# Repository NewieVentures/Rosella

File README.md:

# Rosella (code name Project Faraday)
### By NewieVentures

Remote control of LED strip lights via DMX over cellular.

## Hardware
### Artifacts
* FP1 - Motherboard
* FP2 - DMX expansion module
* FA1 - Assembled unit
* FA2 - Demonstration panel

## LED patterns
To update the pattern of an active device, the device ID and a valid access token is required:

`curl -v "https://api.particle.io/v1/devices/<DEVICE_ID>/<function>" -d access_token=<TOKEN> -d arg=<ARG>`

eg to set a green strobe at 1Hz:

`curl -v "https://api.particle.io/v1/devices/<your device ID here>/strobe" -d access_token=<your access token here> -d arg="1000,#00FF00"`

### Blink
Flash LEDs on and off. Duty cycle controls amount of time on vs off.
#### Arguments
`"<period (ms)>,<duty cycle (0-100)>,<colour-on>,<colour-off>"`

eg blink red 1s:

`POST /v1/devices/:deviceId/blink { "arg": "1000,50,#FF0000,#000000" }`

### Colour
Fixed colour on all leds
#### Arguments
`"<colour>"`

Eg all LEDS blue:

`POST /v1/devices/:deviceId/colour { "arg": "#0000FF" }`

### Gradient
Linear colour gradient
#### Arguments
`"<start-colour>,<end-colour>"`

eg gradient on all LEDS from red to green:

`POST /v1/devices/:deviceId/gradient { "arg": "#FF0000,#00FF00" }`

### Progress
Progress bar
#### Arguments
* Initial value: 0 - (# leds – 1)
* Final value: 1 - #leds
* Direction: 0 = first LED to last, 1 = last LED to first

`"<initial value>,<final value><increment (# leds)>,<increment delay (ms)>,<reset delay(ms)>,<direction>,<colour-on>,<colour-off>"`

eg Progress bar from 0 to 100 leds with 1s between increments, 5s pause at the final value
before repeating and starting from the first LED to the last, incrementing by 1 LED with
RED being on and black being off:

```
POST /v1/devices/:deviceId/progress
{ "arg": "0,100,1,1000,5000,0,#FF0000,#000000" }
```

### Snake
Block of LEDS moving along the strip.
#### Arguments
* Direction: 0 = first LED to last, 1 = last LED to first
`"<period (ms)>,<direction>,<length (# leds)>,<colour-on>,<colour-off>"`

eg Green block of 3 LEDS moving from first LED to last every 5s on a black background:

`POST /v1/devices/:deviceId/snake { "arg": "5000,0,3,#00FF00,#000000" }`

### Strobe
Flash LEDs
#### Arguments
`"<period (ms)>,<colour>"`

eg Blue flash at 1Hz

`POST /v1/devices/:deviceId/strobe { "arg": "1000,#0000FF" }`

## Firmware
The firmware is compiled using the particle cloud development tools (internet connection required).

### Setup
Install the particle CLI, see docs at
https://docs.particle.io/tutorials/developer-tools/cli/

### Compiling
To compile using the particle CLI:
`particle compile electron app --saveTo electron.bin`

### Flashing
To flash a binary to the module over USB, put it into programming mode then:
`particle flash --usb electron.bin`

### Unit tests
```
cd src
make tests && ./tests
```

### Structure
The firmware runs on a Particle Electron board, using their Device OS.  The major firmware modules are:
* cloudFunctions - functions registered with Particle's Device OS on boot and called via their cloud interface.
* LedStripDriver - generates colour values for each LED based on the pattern and settings.  The cloud functions change the pattern settings, while a timer in the RTOS calls the onTimerFired() method to process the new values.
* dmx - uses Serial1 to send the DMX packets (requires some low level override of the baud rate to send the break and mark-after-break at the start of the packet) and sends the NULL start code in each packet.

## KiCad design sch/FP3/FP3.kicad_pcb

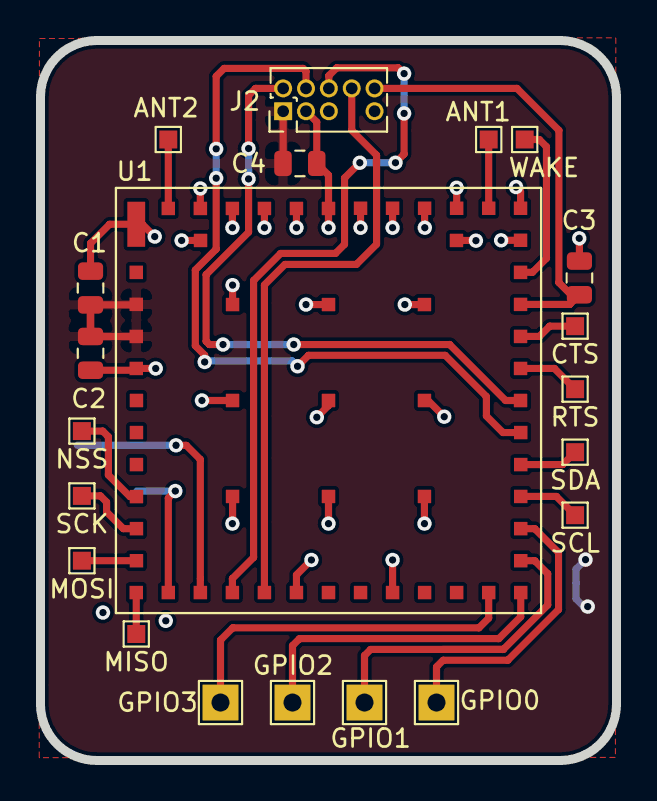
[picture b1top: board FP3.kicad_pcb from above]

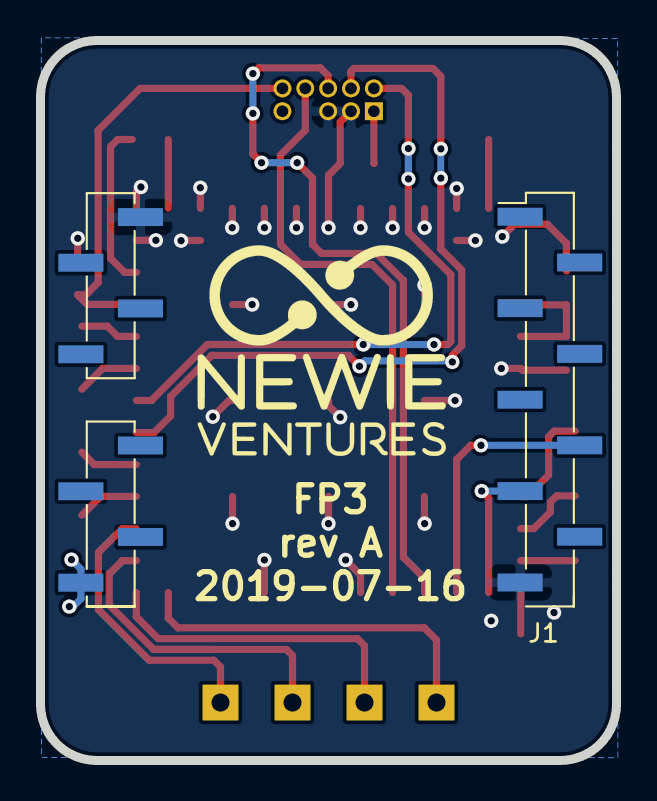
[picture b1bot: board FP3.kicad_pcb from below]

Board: 2 copper layers, 32.0 x 40.0 mm, 23 parts (2 on the bottom side), 24 nets.

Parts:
C1: 10uF 10V; R_0805_2012Metric
C2, C3, C4: 100nF 50V; R_0805_2012Metric
G1: Logo-NewieVentures-75px; logo_14.2x12.1mm
J1: module_connector_header; Faraday_module_smt_hdr
J2: MXDOT_Prog_Header_Keyed; Header_MDOT_PROG_2x05_Pitch1.27mm
TP1: GPIO3; TestPoint_THTPad_2.0x2.0mm_Drill1.0mm
TP2: GPIO2; TestPoint_THTPad_2.0x2.0mm_Drill1.0mm
TP3: GPIO1; TestPoint_THTPad_2.0x2.0mm_Drill1.0mm
TP4: GPIO0; TestPoint_THTPad_2.0x2.0mm_Drill1.0mm
TP5: WAKE; TestPoint_Pad_1.0x1.0mm
TP6: NSS; TestPoint_Pad_1.0x1.0mm
TP7: SCK; TestPoint_Pad_1.0x1.0mm
TP8: MOSI; TestPoint_Pad_1.0x1.0mm
TP9: CTS; TestPoint_Pad_1.0x1.0mm
TP10: MISO; TestPoint_Pad_1.0x1.0mm
TP11: RTS; TestPoint_Pad_1.0x1.0mm
TP12: SCL; TestPoint_Pad_1.0x1.0mm
TP13: SDA; TestPoint_Pad_1.0x1.0mm
TP14: ANT1; TestPoint_Pad_1.0x1.0mm
TP15: ANT2; TestPoint_Pad_1.0x1.0mm
U1: MTXDOT-AU1-A01-100; MTXDOT-AS1-A00-1

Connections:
+3V3: C1.1, C2.1, C4.1, J1.10, J2.1, U1.3, U1.4
/MBED_RX: J2.6, U1.15
/MBED_TX: J2.8, U1.16
/NRESET: C3.1, J2.10, U1.33
/SWCLK: J2.4, U1.29
/SWDIO: J2.2, U1.30
/UART_RX: J1.7, U1.13
/UART_TX: J1.6, U1.14
GND: C1.2, C2.2, C3.2, C4.2, J1.9, J1.17, J2.3, J2.5, U1.1, U1.5, U1.17, U1.20, U1.35, U1.36, U1.38, U1.39, U1.40, U1.41, U1.42, U1.43, U1.44, U1.45, U1.46, U1.48, U1.49, U1.50, U1.51, U1.52, U1.53, U1.54, U1.55, U1.56, U1.57, U1.58
unnamed: TP1.1, U1.23
unnamed: TP2.1, U1.24
unnamed: TP3.1, U1.25
unnamed: TP4.1, U1.26
unnamed: TP5.1, U1.34
unnamed: TP6.1, U1.9
unnamed: TP7.1, U1.10
unnamed: TP8.1, U1.11
unnamed: TP9.1, U1.32
unnamed: TP10.1, U1.12
unnamed: TP11.1, U1.31
unnamed: TP12.1, U1.27
unnamed: TP13.1, U1.28
unnamed: TP14.1, U1.37
unnamed: TP15.1, U1.47

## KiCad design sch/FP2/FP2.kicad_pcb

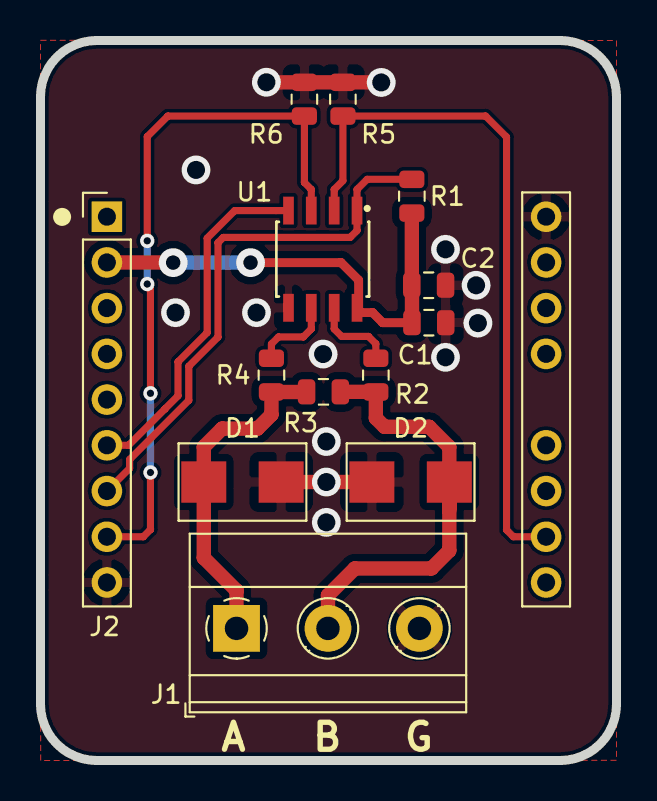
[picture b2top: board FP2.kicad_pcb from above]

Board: 2 copper layers, 32.0 x 40.0 mm, 13 parts (0 on the bottom side), 10 nets.

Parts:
C1: 10uF 10V; R_0805_2012Metric
C2: 100nF 50V; R_0805_2012Metric
D1, D2: 43V 600W; D_SMB_NP
J1: DMX OUT; TerminalBlock_Phoenix_MKDS-1,5-3-5.08_1x03_P5.08mm_Horizont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
J2: module_connector_header; Faraday_module
R1, R5, R6: 10k; R_0805_2012Metric
R2, R4: 10R; R_0805_2012Metric
R3: 120R; R_0805_2012Metric
U1: SP485E; SOIC-8_3.9x4.9mm_P1.27mm

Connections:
+5V: C1.1, C2.1, J2.2, R1.2, U1.8
/RS485_DRV_EN: J2.8, R6.2, U1.3
/RS485_RCV_EN: J2.11, R5.2, U1.2
/UART_RX: J2.7, R1.1, U1.1
/UART_TX: J2.6, U1.4
GND: C1.2, C2.2, D1.2, D2.2, J1.3, J2.9, J2.17, R5.1, R6.1, U1.5
unnamed: D1.1, J1.1, R3.1, R4.1
unnamed: D2.1, J1.2, R2.1, R3.2
unnamed: R2.2, U1.7
unnamed: R4.2, U1.6

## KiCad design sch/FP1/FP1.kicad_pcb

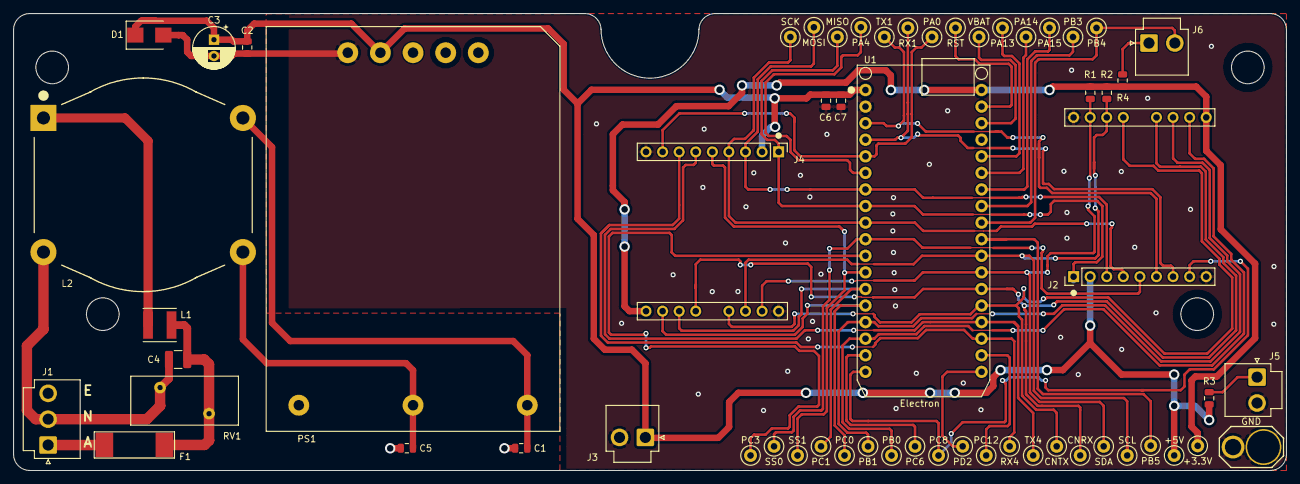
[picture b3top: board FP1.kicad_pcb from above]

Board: 2 copper layers, 195.0 x 70.0 mm, 63 parts (0 on the bottom side), 44 nets.

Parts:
C1, C5: 1nF 400VAC; C_0805_2012Metric
C2: 1uF 50V; C_0805_2012Metric
C3: 470uF 10V; CP_Radial_D6.3mm_P2.50mm
C4: 100nF 275VAC; C_1210_3225Metric
C6: 10uF 10V; C_0805_2012Metric
C7: 100nF 50V; C_0805_2012Metric
D1: 7V 600W; D_SMB
F1: 2A 250V SB; Fuse_SMD_10W_3H
J1: 240V Mains; JST_VH_B3P-VH-B_1x03_P3.96mm_Vertical
J2: Module 0; Faraday_module
J3: 5VDC; JST_VH_B2P-VH_1x02_P3.96mm_Vertical
J4: Module 1; Faraday_module
J5: Power LED; JST_VH_B2P-VH_1x02_P3.96mm_Vertical
J6: Connection LED; JST_VH_B2P-VH_1x02_P3.96mm_Vertical
L1: 4.7uH 2A; L_Taiyo-Yuden_NR-50xx
L2: 10mH 2A; Choke_Schaffner_RN143-02-33.1x32.5mm
MH1, MH2, MH3, MH4: M3; MountingHole_3.5mm
PS1: LHE15-20D0512-04; LHE15-20
R1, R2: 4k7; R_0805_2012Metric
R3, R4: 220R; R_0805_2012Metric
RV1: 300VAC 125J; RV_Disc_D16.5mm_W7.5mm_P7.5mm
TP1: VBAT; TestPoint_Loop_D2.50mm_Drill1.0mm
TP2: PA13; TestPoint_Loop_D2.50mm_Drill1.0mm
TP3: RST; TestPoint_Loop_D2.50mm_Drill1.0mm
TP4: PA14; TestPoint_Loop_D2.50mm_Drill1.0mm
TP5: PA15; TestPoint_Loop_D2.50mm_Drill1.0mm
TP6: PC1; TestPoint_Loop_D2.50mm_Drill1.0mm
TP7: PB3; TestPoint_Loop_D2.50mm_Drill1.0mm
TP8: PC0; TestPoint_Loop_D2.50mm_Drill1.0mm
TP9: PB4; TestPoint_Loop_D2.50mm_Drill1.0mm
TP10: PB1; TestPoint_Loop_D2.50mm_Drill1.0mm
TP11: PB5; TestPoint_Loop_D2.50mm_Drill1.0mm
TP12: PB0; TestPoint_Loop_D2.50mm_Drill1.0mm
TP13: PC6; TestPoint_Loop_D2.50mm_Drill1.0mm
TP14: TX1; TestPoint_Loop_D2.50mm_Drill1.0mm
TP15: PC8; TestPoint_Loop_D2.50mm_Drill1.0mm
TP16: RX1; TestPoint_Loop_D2.50mm_Drill1.0mm
TP17: MOSI; TestPoint_Loop_D2.50mm_Drill1.0mm
TP18: CNTX; TestPoint_Loop_D2.50mm_Drill1.0mm
TP19: MISO; TestPoint_Loop_D2.50mm_Drill1.0mm
TP20: CNRX; TestPoint_Loop_D2.50mm_Drill1.0mm
TP21: SCK; TestPoint_Loop_D2.50mm_Drill1.0mm
TP22: SS0; TestPoint_Loop_D2.50mm_Drill1.0mm
TP23: SDA; TestPoint_Loop_D2.50mm_Drill1.0mm
TP24: SCL; TestPoint_Loop_D2.50mm_Drill1.0mm
TP25: PA0; TestPoint_Loop_D2.50mm_Drill1.0mm
TP26: PA4; TestPoint_Loop_D2.50mm_Drill1.0mm
TP27: TX4; TestPoint_Loop_D2.50mm_Drill1.0mm
TP28: PC3; TestPoint_Loop_D2.50mm_Drill1.0mm
TP29: RX4; TestPoint_Loop_D2.50mm_Drill1.0mm
TP30: SS1; TestPoint_Loop_D2.50mm_Drill1.0mm
TP31: PC12; TestPoint_Loop_D2.50mm_Drill1.0mm
TP32: PD2; TestPoint_Loop_D2.50mm_Drill1.0mm
TP33: +5V; TestPoint_Loop_D2.50mm_Drill1.0mm
TP34: GND; Test_Point_Alligator_Clip_And_Probe
TP35: +3.3V; TestPoint_Loop_D2.50mm_Drill1.0mm
U1: Electron; PARTICLE_ELECTRON

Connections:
+3V3: J2.10, J4.10, R1.1, R2.1, R4.2, TP35.1, U1.36
+5V: C2.1, C3.1, C6.1, C7.1, D1.1, J2.2, J3.1, J4.2, PS1.7, R3.2, TP33.1, U1.1
/A1_PC3: TP28.1, U1.11
/B0_PC8: J2.8, TP15.1, U1.18
/B1_PC6: TP13.1, U1.17
/B2_PB0: J2.11, TP12.1, U1.16
/B3_PB1: J2.12, TP10.1, U1.15
/B4_PC0: J4.11, TP8.1, U1.14
/B5_PC1: J4.12, TP6.1, U1.13
/C0_PD2: TP32.1, U1.19
/C1_PC12: TP31.1, U1.20
/CAN_RX: J2.13, J4.13, TP20.1, U1.24
/CAN_TX: J2.14, J4.14, TP18.1, U1.23
/D2_PB5: TP11.1, U1.27
/D3_PB4: J6.2, TP9.1, U1.28
/D4_PB3: TP7.1, U1.29
/D5_PA15: TP5.1, U1.30
/D6_PA14: TP4.1, U1.31
/D7_PA13: TP2.1, U1.32
/DAC_PA4: TP26.1, U1.6
/I2C_SCL: J2.15, J4.15, R2.2, TP24.1, U1.26
/I2C_SDA: J2.16, J4.16, R1.2, TP23.1, U1.25
/RESET: TP3.1, U1.35
/SPI_MISO: J2.1, J4.1, TP19.1, U1.8
/SPI_MOSI: J2.3, J4.3, TP17.1, U1.7
/SPI_SCK: J2.4, J4.4, TP21.1, U1.9
/SPI_SS0: J2.5, TP22.1, U1.10
/SPI_SS1: J4.5, TP30.1, U1.12
/UART1_RX: J2.7, TP16.1, U1.4
/UART1_TX: J2.6, TP14.1, U1.3
/UART4_RX: J4.7, TP29.1, U1.21
/UART4_TX: J4.6, TP27.1, U1.22
/VBAT: TP1.1, U1.34
/WKP_PA0: J4.8, TP25.1, U1.5
Earth: C1.2, C5.1, J1.3, PS1.1
GND: C2.2, C3.2, C6.2, C7.2, D1.2, J2.9, J2.17, J3.2, J4.9, J4.17, J5.2, PS1.8, TP34.1, U1.2, U1.33
unnamed: C1.1, L2.2, PS1.3
unnamed: C4.1, F1.1, L1.1, RV1.1
unnamed: C4.2, J1.2, L2.3, RV1.2
unnamed: C5.2, L2.4, PS1.2
unnamed: F1.2, J1.1
unnamed: J5.1, R3.1
unnamed: J6.1, R4.1
unnamed: L1.2, L2.1

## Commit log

2019-06-24 Added base code from Obelisk repo.
2019-06-24 Added gitignore, license and readme.
2019-06-24 Implemented default loop pattern.
2019-06-24 Started implementing wind pattern.
2019-06-25 Finished wind pattern with tests.
2019-06-25 Refactored wind pattern.
2019-06-25 Change to defaultLoop pattern on activity timeout.
2019-07-02 Removed rogue space.
2019-07-02 Added weather warning to wind pattern with tests.
2019-07-05 Added cloud function for default loop with tests.
2019-07-05 Added cloud function for wind pattern with tests.
2019-07-05 Added tests for weather cloud function.
2019-07-05 Refactored wind pattern code.
2019-07-07 Refactored default loop pattern.
2019-07-08 Refactored weather pattern.
2019-07-08 Refactored pulse, gradient and snake patterns.
2019-07-08 Added RGBW compatibility.
2019-07-08 Moved func reg to separate function, need to init object first for tests.
2019-07-08 Added state reset and fade to new wind direction colour.
2019-07-08 Restored status LED functionality (broken as part of RGBW work).
2019-07-09 Designed seeeduino mounting bracket for button enclosure.
2019-07-15 Started FP3 PCB layout.
2019-07-16 Finished FP3 sch and PCB, updated title blocks.
2019-07-16 Added test points and connector details for FP3.
2019-07-30 Added code for the seeeduino LoRa button.
2019-08-13 Added LoRa daughter board firmware (xDot).
2019-08-13 Added firmware for LoRa button (mDot based).
2019-09-03 Finalised mounting plate for LoRa button.
2019-11-21 Updated readme with new name (Rosella).
2019-12-12 Implemented air quality pattern with tests.
2019-12-12 Implemented air quality cloud function with tests.
2020-01-09 Refactored toggle switch setup and handled initialisation of layer.
2020-01-13 Enabled pattern timeout for weather, wind and air patterns.
2020-01-13 Set 'defaultLoop' as pattern shown on power-up.
